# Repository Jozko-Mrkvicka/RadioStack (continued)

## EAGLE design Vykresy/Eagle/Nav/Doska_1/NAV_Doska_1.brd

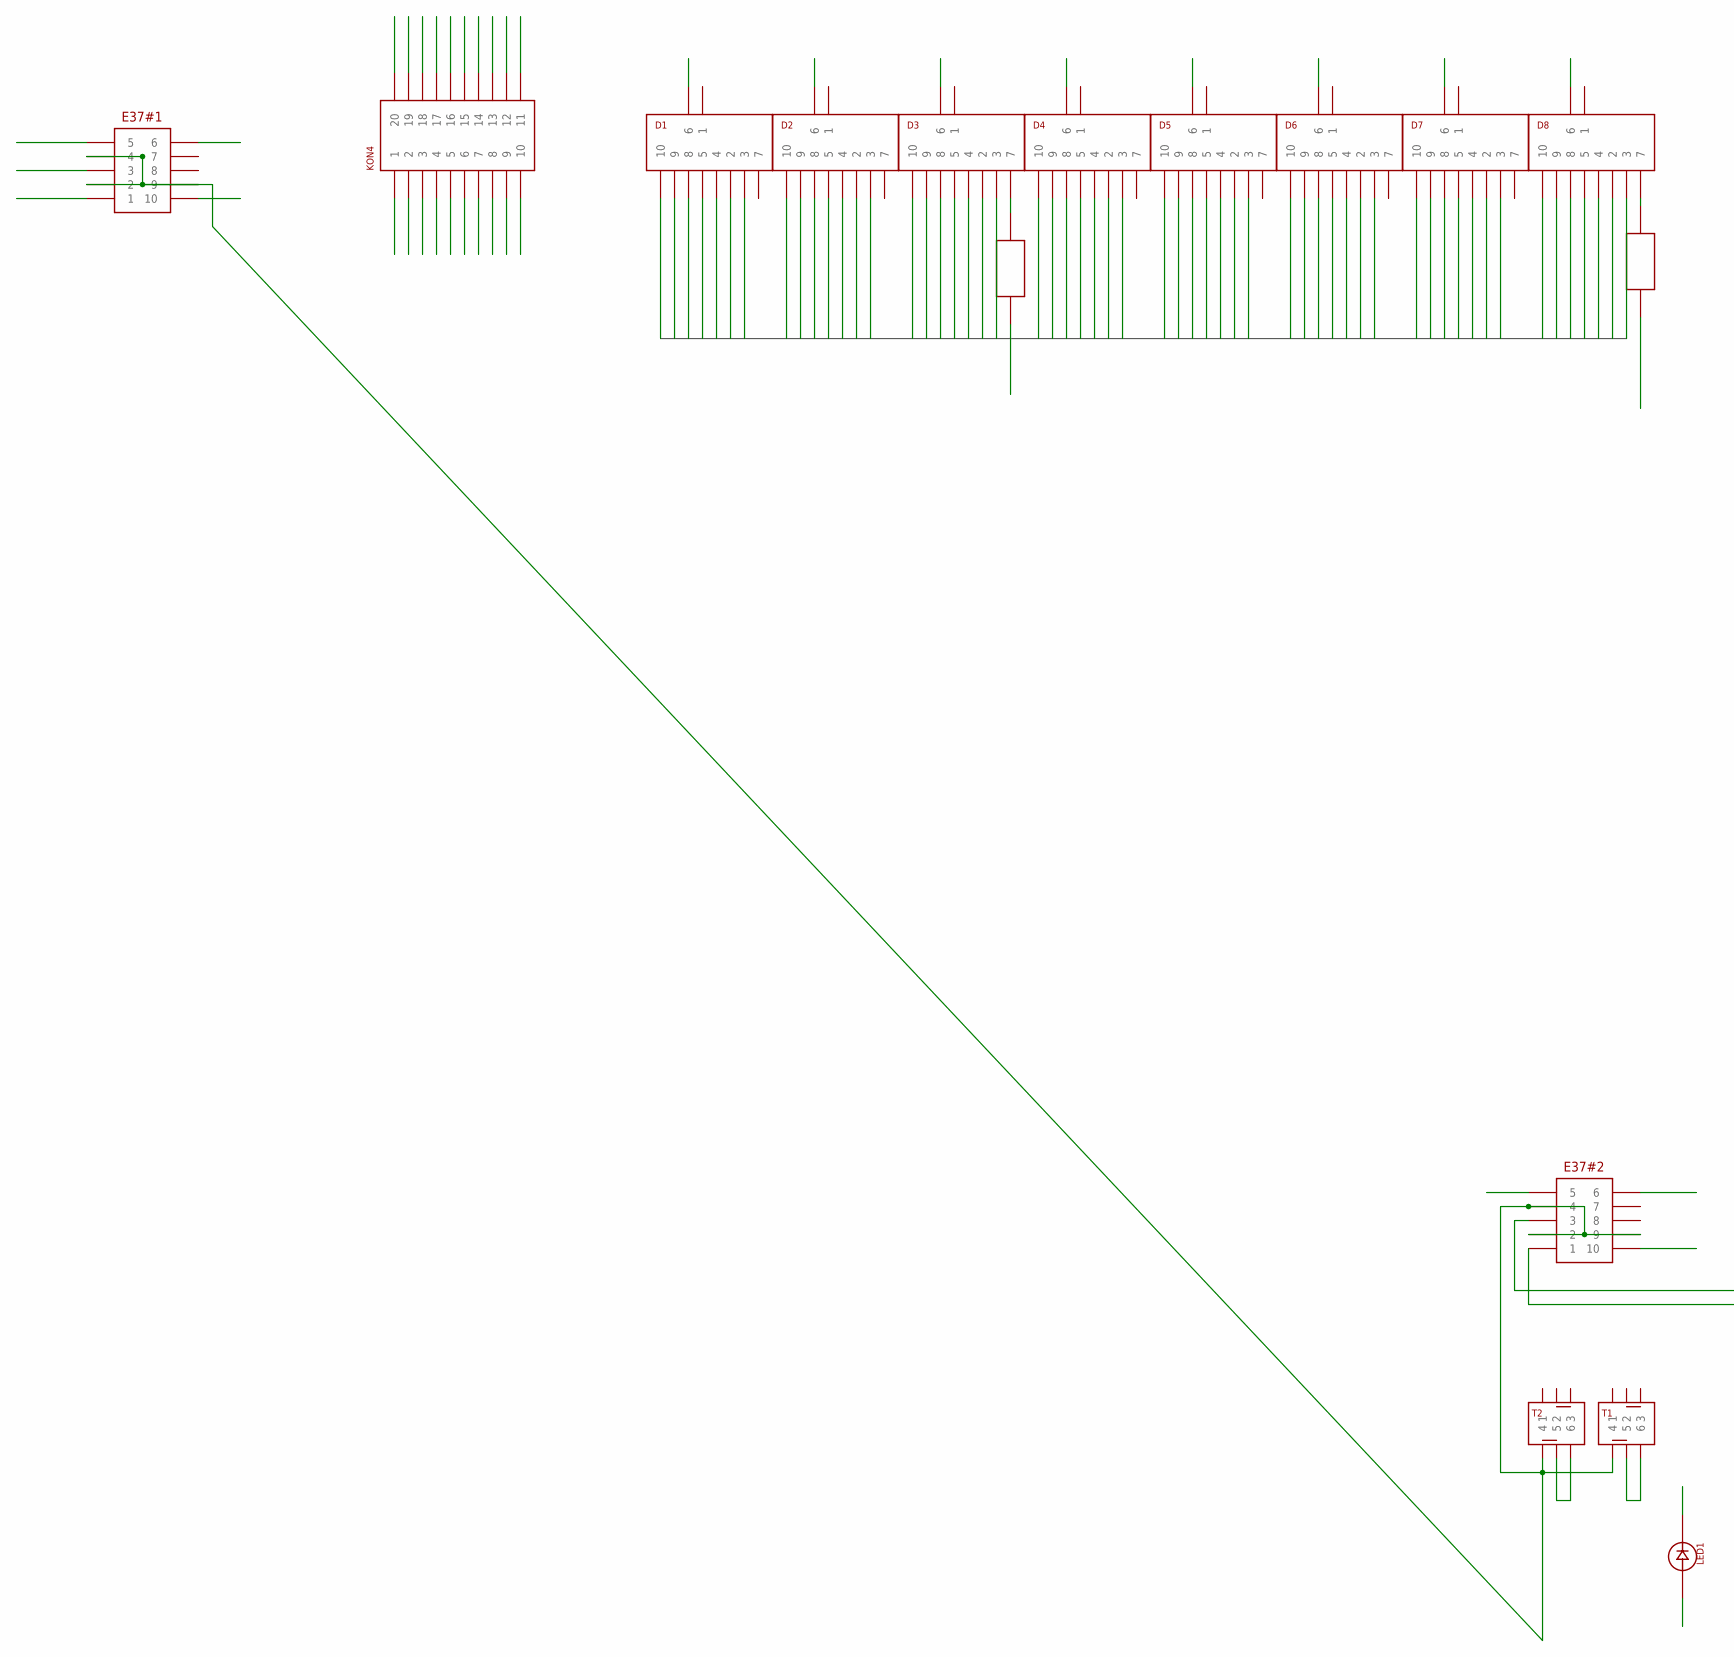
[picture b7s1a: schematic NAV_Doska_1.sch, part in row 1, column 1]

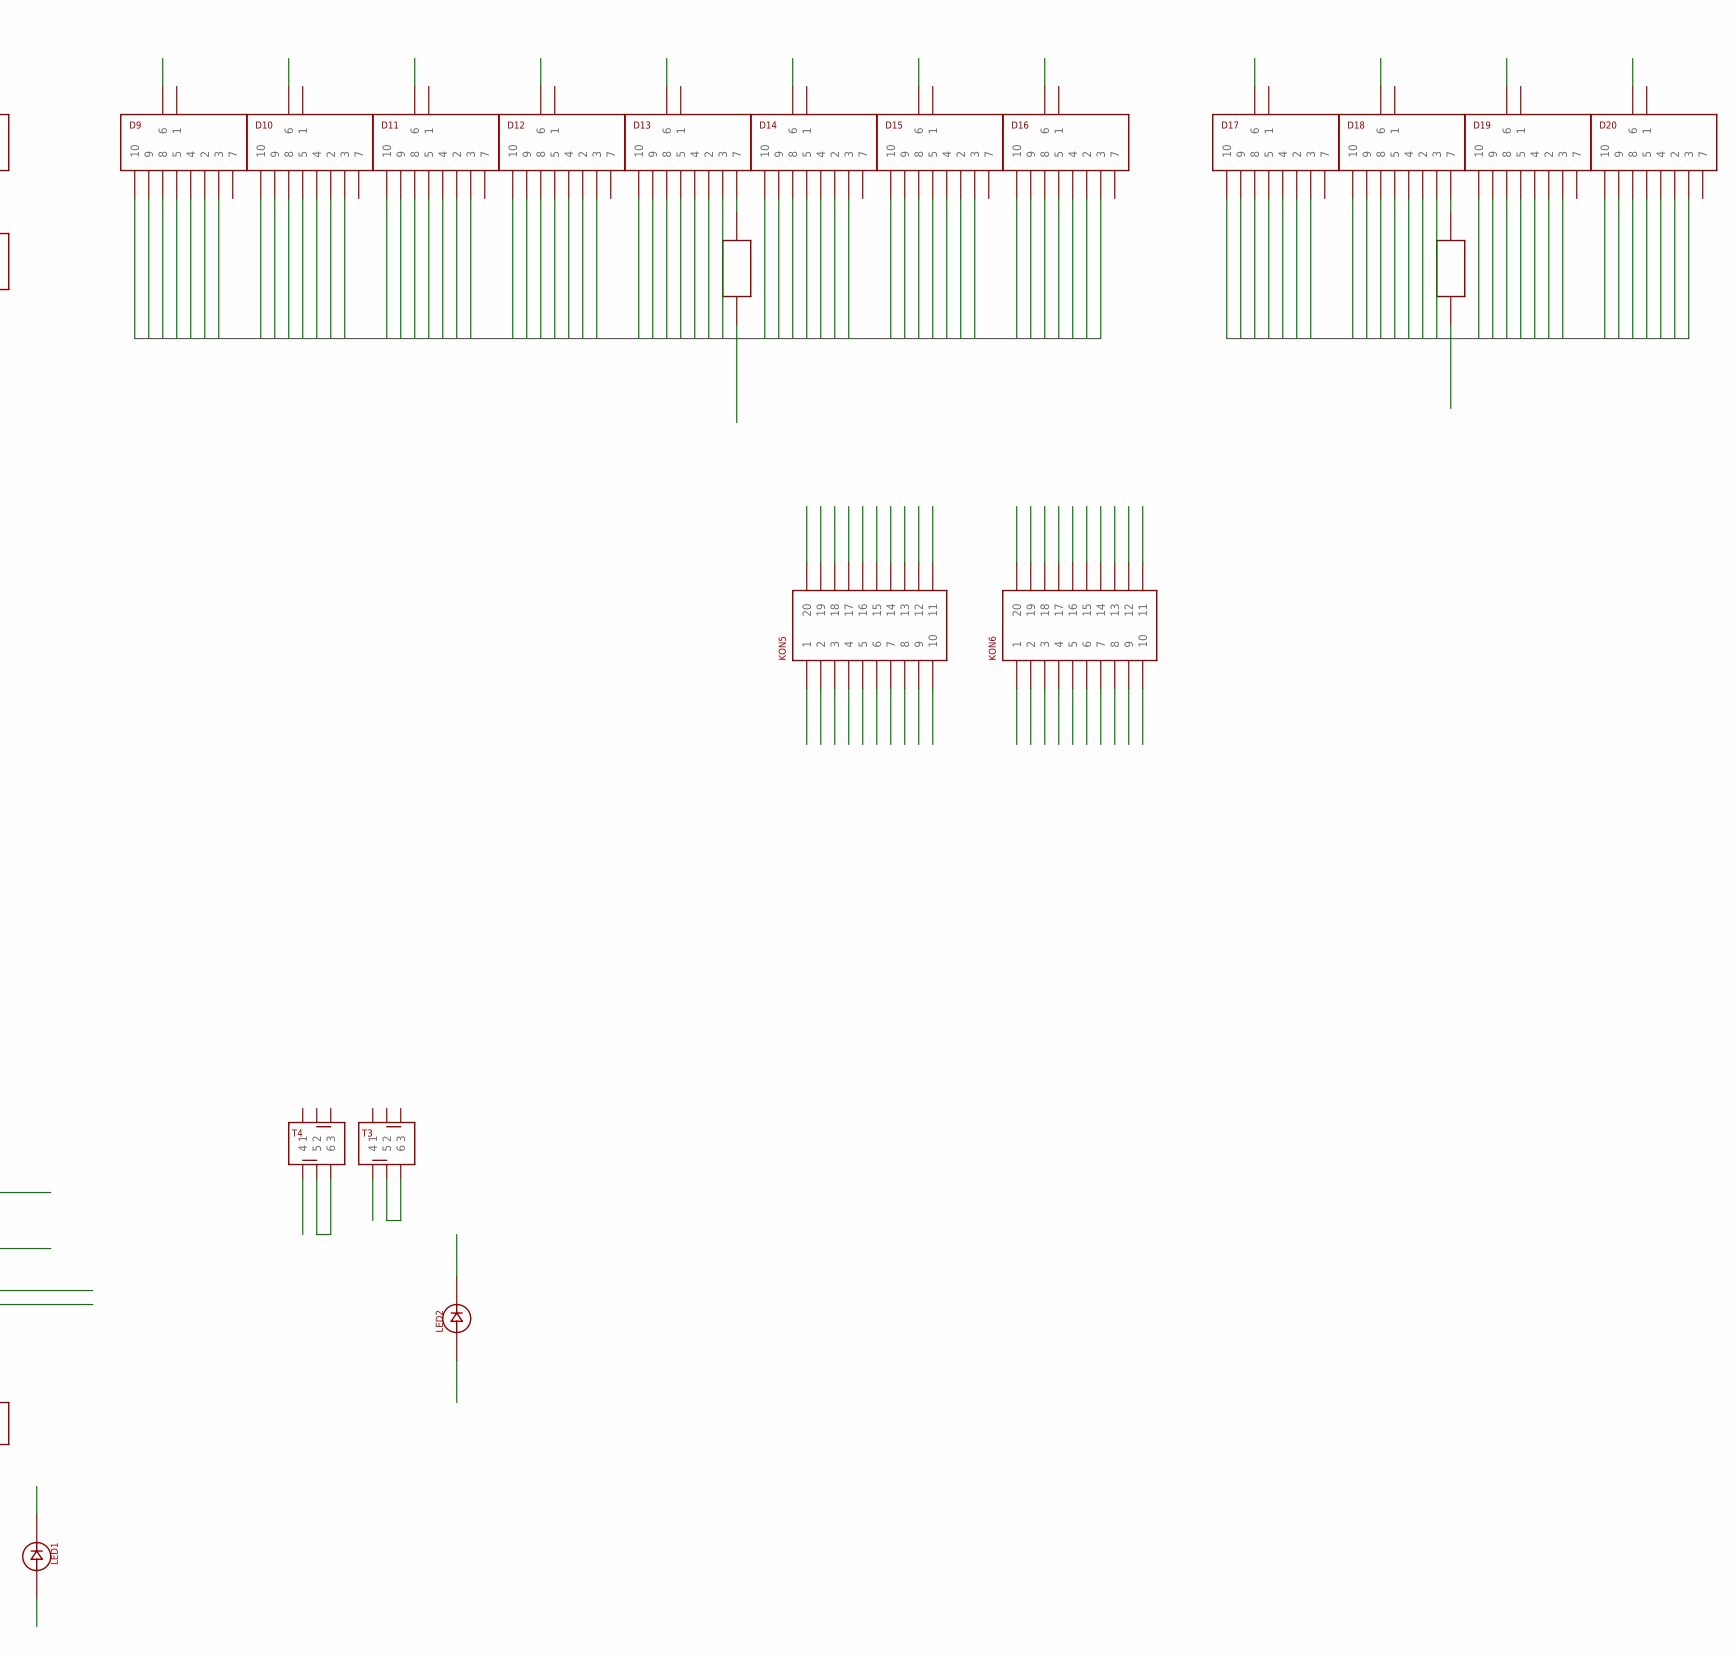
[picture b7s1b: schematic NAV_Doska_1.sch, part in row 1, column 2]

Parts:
D1, D2, D3, D4, D5, D6, D7, D8, D9, D10, D11, D12, D13, D14, D15, D16, D17, D18, D19, D20: SA3611EWA
E37#1, E37#2: ELMA_E37
KON4, KON5, KON6: LISTA_2X10
LED1, LED2: LED_5MM
T1, T2, T3, T4: P1-0S
U$1, U$2, U$3, U$4: REZISTOR

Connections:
D1: D1.6, KON4.1
D2: D2.6, KON4.2
D3: D3.6, KON4.9
D4: D4.6, KON4.6
D5: D5.6, KON4.3
D6: D6.6, KON4.8
D7: D7.6, KON4.7
D8: D8.6, KON4.4
D9: D9.6, KON5.1
D10: D10.6, KON5.2
D11: D11.6, KON5.9
D12: D12.6, KON5.6
D13: D13.6, KON5.3
D14: D14.6, KON5.8
D15: D15.6, KON5.7
D16: D16.6, KON5.4
D17: D17.6, KON6.1
D18: D18.6, KON6.2
D19: D19.6, KON6.9
D20: D20.6, KON6.6
DRIVER1_SEG2: D1.2, D2.2, D3.2, D4.2, D5.2, D6.2, D7.2, D8.2, KON4.10
DRIVER1_SEG3: D1.3, D2.3, D3.3, D4.3, D5.3, D6.3, D7.3, D8.3, KON4.12
DRIVER1_SEG4: D1.4, D2.4, D3.4, D4.4, D5.4, D6.4, D7.4, D8.4, KON4.15
DRIVER1_SEG5: D1.5, D2.5, D3.5, D4.5, D5.5, D6.5, D7.5, D8.5, KON4.16
DRIVER1_SEG8: D1.8, D2.8, D3.8, D4.8, D5.8, D6.8, D7.8, D8.8, KON4.14
DRIVER1_SEG9: D1.9, D2.9, D3.9, D4.9, D5.9, D6.9, D7.9, D8.9, KON4.11
DRIVER1_SEG10: D1.10, D2.10, D3.10, D4.10, D5.10, D6.10, D7.10, D8.10, KON4.13
DRIVER2_SEG2: D9.2, D10.2, D11.2, D12.2, D13.2, D14.2, D15.2, D16.2, KON5.10
DRIVER2_SEG3: D9.3, D10.3, D11.3, D12.3, D13.3, D14.3, D15.3, D16.3, KON5.12
DRIVER2_SEG4: D9.4, D10.4, D11.4, D12.4, D13.4, D14.4, D15.4, D16.4, KON5.15
DRIVER2_SEG5: D9.5, D10.5, D11.5, D12.5, D13.5, D14.5, D15.5, D16.5, KON5.16
DRIVER2_SEG8: D9.8, D10.8, D11.8, D12.8, D13.8, D14.8, D15.8, D16.8, KON5.14
DRIVER2_SEG9: D9.9, D10.9, D11.9, D12.9, D13.9, D14.9, D15.9, D16.9, KON5.11
DRIVER2_SEG10: D9.10, D10.10, D11.10, D12.10, D13.10, D14.10, D15.10, D16.10, KON5.13
DRIVER3_SEG2: D17.2, D18.2, D19.2, D20.2, KON6.10
DRIVER3_SEG3: D17.3, D18.3, D19.3, D20.3, KON6.12
DRIVER3_SEG4: D17.4, D18.4, D19.4, D20.4, KON6.15
DRIVER3_SEG5: D17.5, D18.5, D19.5, D20.5, KON6.16, LED1.P$2, LED2.P$2
DRIVER3_SEG8: D17.8, D18.8, D19.8, D20.8, KON6.14
DRIVER3_SEG9: D17.9, D18.9, D19.9, D20.9, KON6.11
DRIVER3_SEG10: D17.10, D18.10, D19.10, D20.10, KON6.13
E37#1_1: E37#1.1, KON4.17
E37#1_3: E37#1.3, KON4.18
E37#1_5: E37#1.5, KON4.20
E37#1_6: E37#1.6, KON4.19
E37#1_10: E37#1.10, KON4.5
E37#2_1: E37#2.1, KON6.17
E37#2_3: E37#2.3, KON6.18
E37#2_5: E37#2.5, KON6.20
E37#2_6: E37#2.6, KON6.19
E37#2_10: E37#2.10, KON6.5
GND: E37#1.2, E37#1.4, E37#1.9, E37#2.2, E37#2.4, E37#2.9, KON5.5, T1.4, T2.4, T3.5, T3.6, T4.5, T4.6, U$1.P$1, U$2.P$1, U$3.P$1, U$4.P$1
LED1: KON6.3, LED1.P$1
LED2: KON6.8, LED2.P$1
unnamed: D3.7, U$4.P$2
unnamed: D18.7, U$2.P$2
unnamed: D13.7, U$1.P$2
unnamed: D8.7, U$3.P$2
T1: KON5.20, T1.5, T1.6
T2: KON5.19, T2.5, T2.6
T3: KON5.18, T3.4
T4: KON5.17, T4.4

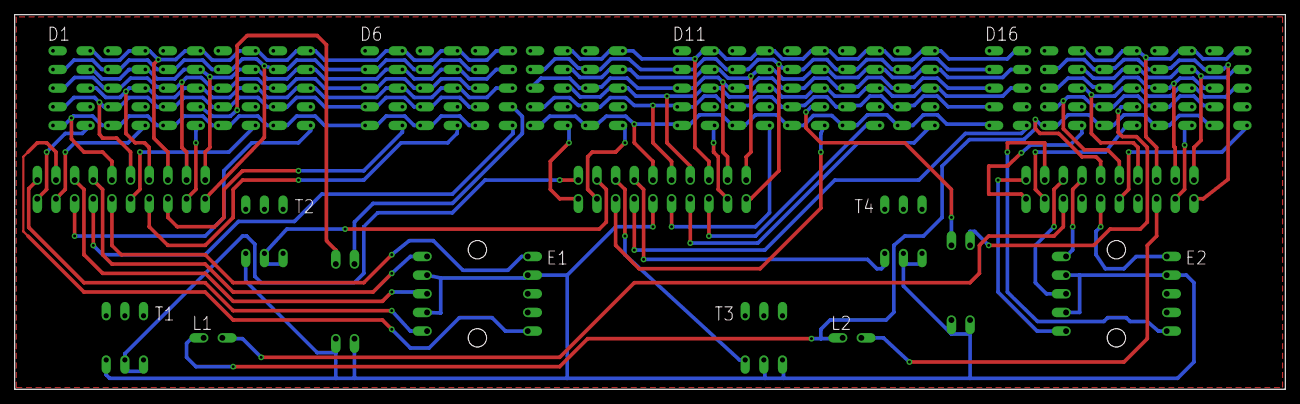
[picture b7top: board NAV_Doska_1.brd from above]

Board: 2 copper layers, 173.0 x 51.0 mm, 35 parts (0 on the bottom side), 62 nets.

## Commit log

2020-05-02 Initial commit. Files were taken from SVN repository without history. Only tags will be copied. This is tag #1.
2020-05-02 This is tag #2 taken from former SVN repository.
2020-05-02 This is tag #3 taken from former SVN repository.
2020-05-02 This is tag #4 taken from former SVN repository.
2020-05-02 This is the latest state of the project as it was found on my local drive.
2020-05-08 Both XPDR boards finished.
2020-05-10 - DME module finished. - Problem with incorrect pins (RST, INT) in XPDR module fixed.
2020-07-10 The file .gitignore added to the project.
2020-07-10 The file .gitignore modified.
2020-07-11 Autogenerated files (.o, .hex, .elf) removed from index area of git (changed to untracked).
2020-07-11 Makefiles updated - added option "shell = cmd" to fix problem with execution of the clean target (cmd commands) under Windows 10.
2020-07-14 - Delay in the input read block decreased to 15ms. - Timeout added to the function twi_receive_byte(). - Type char changed to uint8_t. - Type boolean added instead of the int type. - Functions rename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
2020-07-14 - Function display_driver_convert_data() merged to function navcomm_output(). - Function display_driver_select_write_signal() deleted. - Helper functions changed to static.
2020-07-14 File icm7228_driver.c renamed to icm7228.c.
2020-07-14 - Created new common module mcp23016. All related functions and definitions moved to it. - Deleted unused common module packing.
2020-07-15 The usart module polished.
2020-07-16 Created very basic communication with host terminal: - Created "protocol" for receive from terminal to the device. Six bytes are transmitted, one command byte to select display + five bytes of the ou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
2020-07-16 - All inputs and outputs fully work with a host terminal interface (but only if both modules, NavComm1 and NavComm2, are connected). - If only one modul is connected then inputs don`t work as expecte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
2020-07-17 - All inputs and outputs fully work with a host terminal interface. - New function is_module_connected() was created. Now it doesn`t matter if both modules (NavComm1 and NavComm2) are connected or no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
2020-07-17 - Added output control from host for LEDs. - Created new function send_input_to_host(). - Deleted unused common files (datatypes.h, iopin.c, iopin.h).
2020-07-18 Added README.md file.
2020-08-05 Deleted whole RS2FSX project (Visual Studio project with all files). It will be replaced with new version written in GCC (under MINGW).
2020-08-05 - Added new version of rs2fsx project. - Written in MinGW GCC. - All displays and all rotary encoders in NavComm1 module are working together with FSX. - Buttons not implemented yet.
2020-08-08 - All related functions from rs2fsx.c moved to new module rs2fsx_navcomm.c. - Unused data structures and fuctions in rs2fsx.c deleted.
2020-08-08 - All COM port related functions moved to new modul rs2fsx_comport.c. - Added new function rs2fsx_init_display(). - Added new function rs2fsx_heartbeat(). - Encoders in navcomm2 module enabled.
2020-08-08 - Solved problem that radiostack was stuck during fast rotation of rotary encoders. - Displays are now automatically updated when simulation is restarted/reloaded. - Buttons enabled (ident and swap) 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
2020-08-09 - Added new function rs2fsx_refresh_display(). Now it is possible to change a radiostack value in simulator and this change is displayed also in HW radiostack. - All of the rotary encoder navcomm fun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
